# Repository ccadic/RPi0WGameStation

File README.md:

# RPi0WGameStation
PCB to make a RPI0 based game station or WIFI remote controler

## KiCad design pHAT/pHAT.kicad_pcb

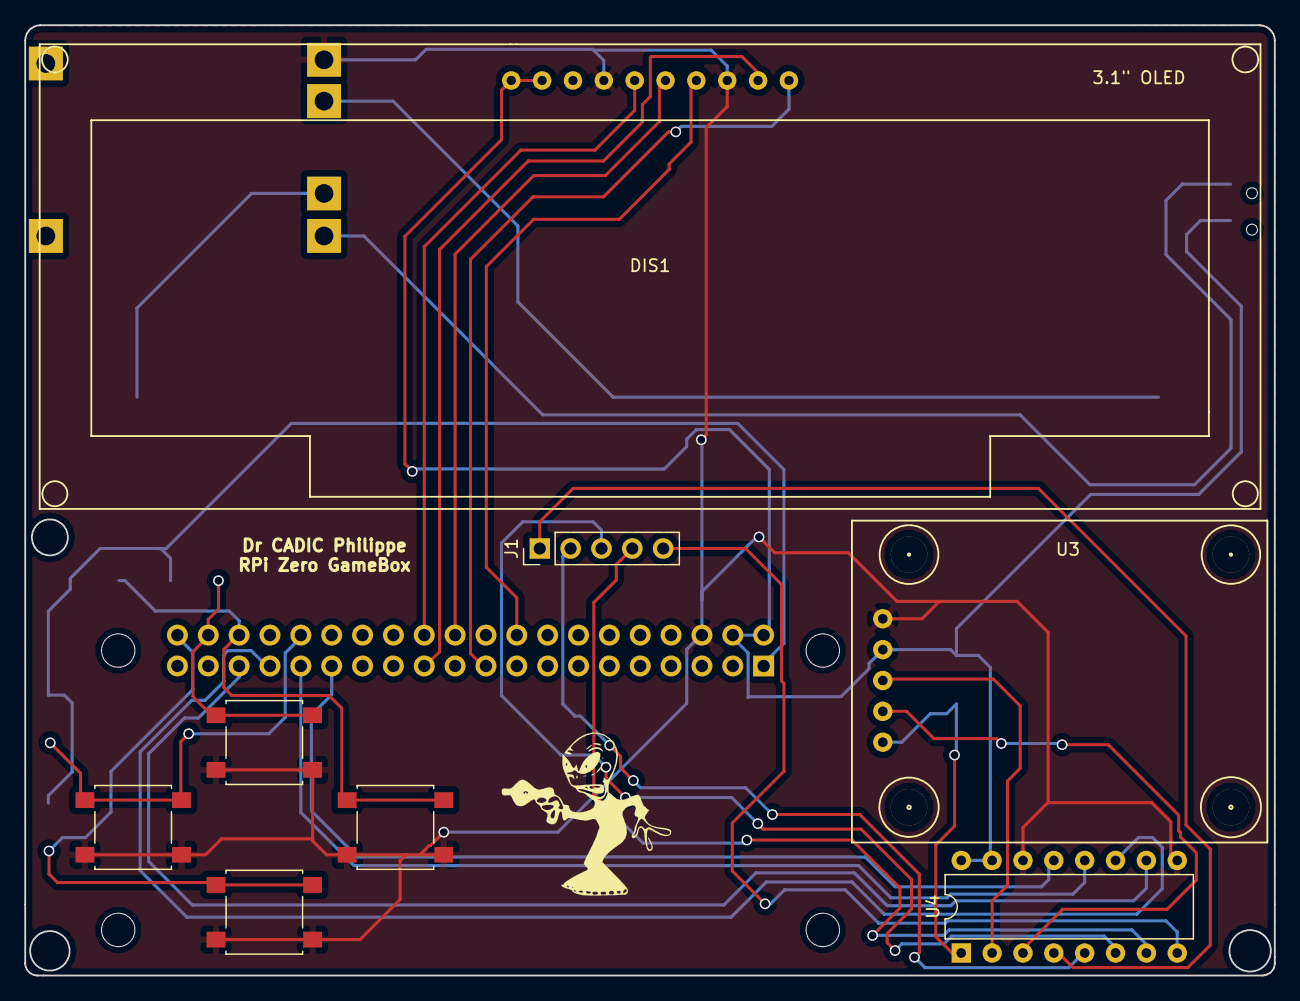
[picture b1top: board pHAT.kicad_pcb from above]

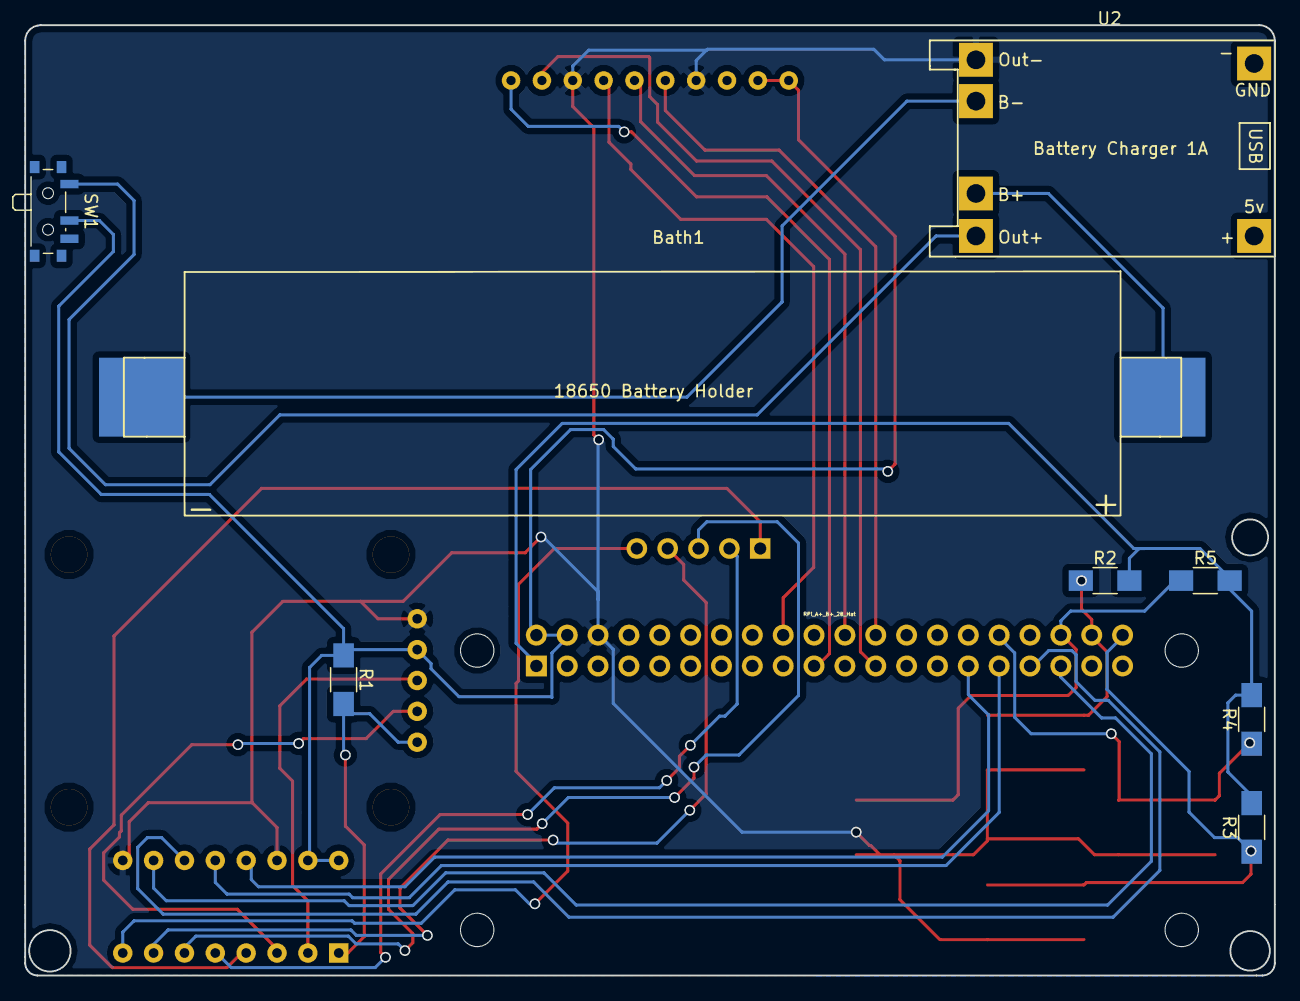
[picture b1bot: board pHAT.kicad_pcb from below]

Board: 2 copper layers, 102.9 x 78.2 mm, 17 parts (9 on the bottom side), 27 nets.

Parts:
Bath1: 18650BattHolder
DIS1: 3.1OLED; 3_1_OLED
J1: ExtraAnlg; Socket_Strip_Straight_1x05_Pitch2.54mm
R1, R2, R3, R4, R5: 10k; R_1206_HandSoldering
SW1: SW_SPST; SW_SPDT_PCM12
SW2: But2; SW_SPST_B3S-1000
SW3: But1; SW_SPST_B3S-1000
SW4: But4; SW_SPST_B3S-1000
SW5: But3; SW_SPST_B3S-1000
U1: RPi_A+_B+_2B_Hat; z_RPiZero_Hat_NPTH
U2: TP4056; TP4056-18650
U3: JoystkAnalog
U4: MCP3008; DIP-16_W7.62mm

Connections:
3.3v: R2.2, R3.2, R4.2, R5.2, U1.1
CLK: U1.29, U4.13
DIN: U1.33, U4.11
DOUT: U1.31, U4.12
GND: DIS1.4, DIS1.8, SW2.2, SW3.2, SW4.2, SW5.2, U1.6, U2.4, U3.1, U4.9, U4.14
GP12: R4.1, SW4.1, U1.32
GP16: R5.1, SW5.1, U1.36
GP20: R2.1, SW2.1, U1.38
GP21: R3.1, SW3.1, U1.40
GPIO24: DIS1.7, U1.18
GPIO25: DIS1.6, U1.22
MOSI: DIS1.10, U1.19
unnamed: Bath1.1, U2.5
unnamed: Bath1.2, U2.6
unnamed: J1.1, U4.4
unnamed: J1.2, U4.5
unnamed: J1.3, U4.6
unnamed: J1.4, U4.7
unnamed: J1.5, U4.8
unnamed: SW1.1, U2.3
SCLK: DIS1.9, U1.23
SHDN: U1.35, U4.10
SS: DIS1.5, U1.24
Switch: R1.2, U3.5, U4.1
VCC: DIS1.1, DIS1.2, R1.1, SW1.2, U1.2, U1.4, U3.2, U4.15, U4.16
VrX: U3.3, U4.2
VrY: U3.4, U4.3

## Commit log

2017-11-20 Create kicad sources
